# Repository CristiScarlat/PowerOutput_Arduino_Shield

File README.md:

# PowerOutput_Arduino_Shield
Arduino Mega Shield 16 x open collector(ULN2803) outputs I2C(MCP23017)

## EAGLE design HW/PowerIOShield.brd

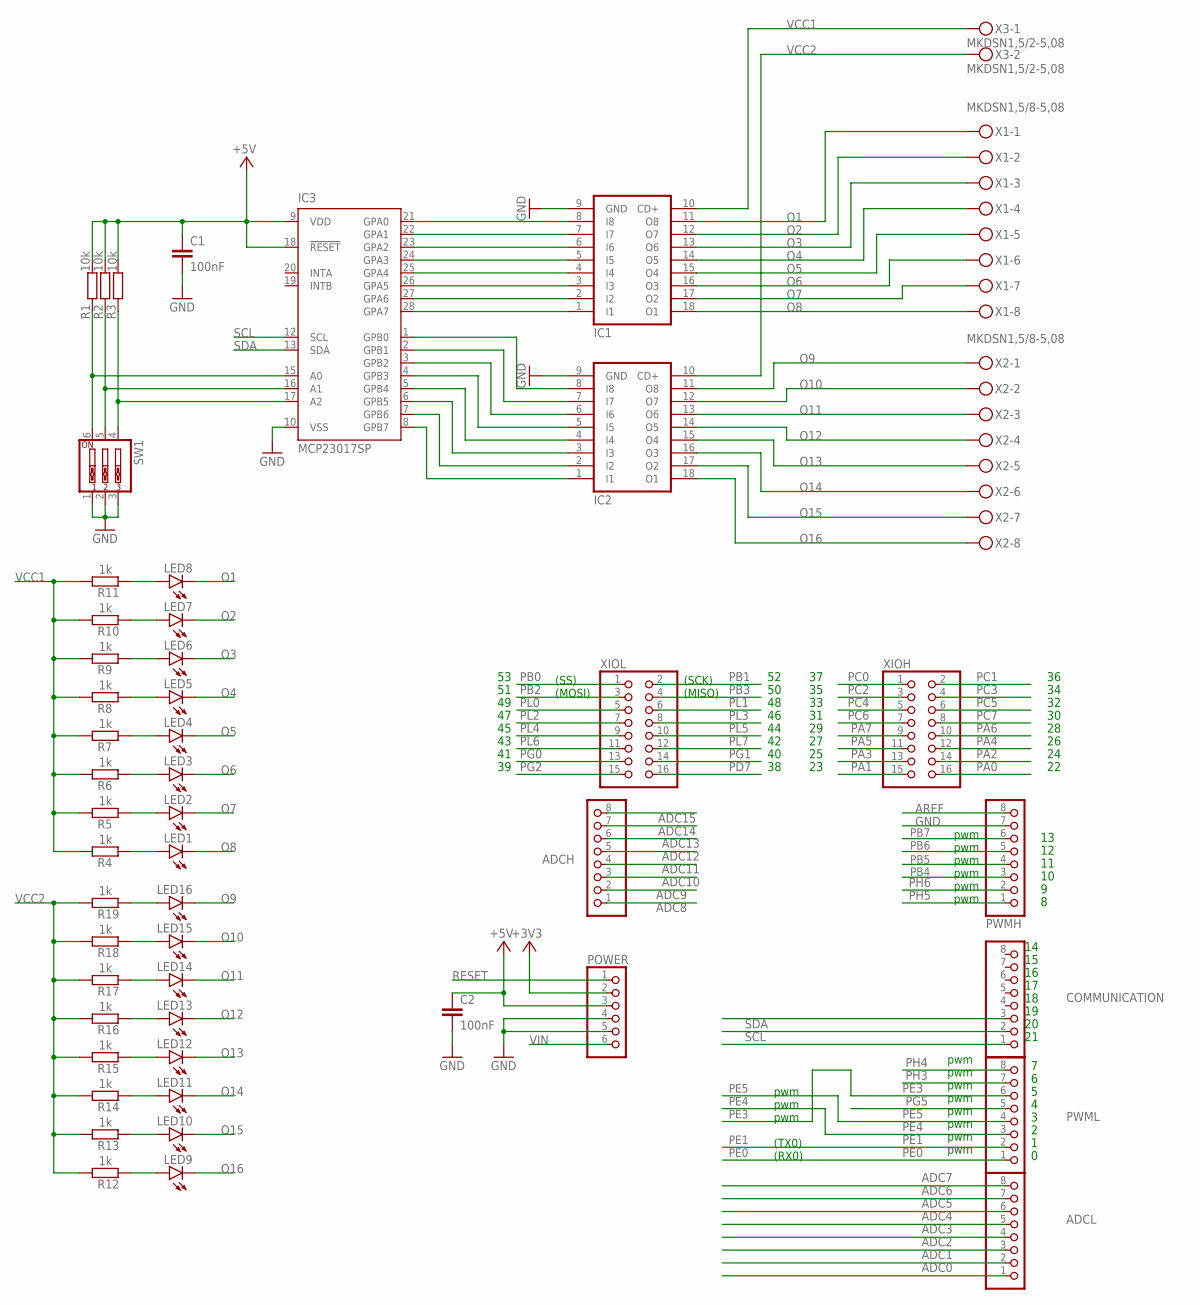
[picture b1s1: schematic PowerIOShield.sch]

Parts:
ADCH: PINHD-1X8; 1X08
ADCL: PINHD-1X8; 1X08
C1, C2: 100nF; C025-024X044
COMMUNICATION: PINHD-1X8; 1X08
IC1, IC2: ULN2803A; DIL18
IC3: MCP23017SP; DIL28-3
LED1, LED2, LED3, LED4, LED5, LED6, LED7, LED8, LED9, LED10, LED11, LED12, LED13, LED14, LED15, LED16: LED3MM
POWER: PINHD-1X6; 1X06
PWMH: PINHD-1X8; 1X08
PWML: PINHD-1X8; 1X08
R1, R2, R3: 10k; 0204/7
R4, R5, R6, R7, R8, R9, R10, R11, R12, R13, R14, R15, R16, R17, R18, R19: 1k; 0204/7
SW1: SW_DIP-3; EDG-03
X1, X2: MKDSN1,5/8-5,08
X3: MKDSN1,5/2-5,08
XIOH: PINHD-2X8; 2X08
XIOL: PINHD-2X8; 2X08

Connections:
+3V3: POWER.2
+5V: C1.1, C2.1, IC3.9 (VDD), IC3.18 (!RESET), POWER.3, R1.2, R2.2, R3.2
ADC0: ADCL.1
ADC1: ADCL.2
ADC2: ADCL.3
ADC3: ADCL.4
ADC4: ADCL.5
ADC5: ADCL.6
ADC6: ADCL.7
ADC7: ADCL.8
ADC8: ADCH.1
ADC9: ADCH.2
ADC10: ADCH.3
ADC11: ADCH.4
ADC12: ADCH.5
ADC13: ADCH.6
ADC14: ADCH.7
ADC15: ADCH.8
AREF: PWMH.8
GND: C1.2, C2.2, IC1.9 (GND), IC2.9 (GND), IC3.10 (VSS), POWER.4, POWER.5, PWMH.7, SW1.1, SW1.2, SW1.3
unnamed: IC3.15 (A0), R1.1, SW1.6
unnamed: IC2.8 (I8), IC3.1 (GPB0)
unnamed: IC1.1 (I1), IC3.28 (GPA7)
unnamed: IC1.2 (I2), IC3.27 (GPA6)
unnamed: IC1.3 (I3), IC3.26 (GPA5)
unnamed: IC1.4 (I4), IC3.25 (GPA4)
unnamed: IC1.5 (I5), IC3.24 (GPA3)
unnamed: IC1.6 (I6), IC3.23 (GPA2)
unnamed: IC1.7 (I7), IC3.22 (GPA1)
unnamed: IC1.8 (I8), IC3.21 (GPA0)
unnamed: IC2.7 (I7), IC3.2 (GPB1)
unnamed: IC2.6 (I6), IC3.3 (GPB2)
unnamed: IC2.5 (I5), IC3.4 (GPB3)
unnamed: IC2.4 (I4), IC3.5 (GPB4)
unnamed: IC2.3 (I3), IC3.6 (GPB5)
unnamed: IC2.2 (I2), IC3.7 (GPB6)
unnamed: IC2.1 (I1), IC3.8 (GPB7)
unnamed: IC3.16 (A1), R2.1, SW1.5
unnamed: IC3.17 (A2), R3.1, SW1.4
unnamed: LED1.A, R4.1
unnamed: LED2.A, R5.1
unnamed: LED3.A, R6.1
unnamed: LED4.A, R7.1
unnamed: LED5.A, R8.1
unnamed: LED6.A, R9.1
unnamed: LED7.A, R10.1
unnamed: LED8.A, R11.1
unnamed: LED9.A, R12.1
unnamed: LED10.A, R13.1
unnamed: LED11.A, R14.1
unnamed: LED12.A, R15.1
unnamed: LED13.A, R16.1
unnamed: LED14.A, R17.1
unnamed: LED15.A, R18.1
unnamed: LED16.A, R19.1
O1: IC1.11 (O8), LED8.K (C), X1.1
O2: IC1.12 (O7), LED7.K (C), X1.2
O3: IC1.13 (O6), LED6.K (C), X1.3
O4: IC1.14 (O5), LED5.K (C), X1.4
O5: IC1.15 (O4), LED4.K (C), X1.5
O6: IC1.16 (O3), LED3.K (C), X1.6
O7: IC1.17 (O2), LED2.K (C), X1.7
O8: IC1.18 (O1), LED1.K (C), X1.8
O9: IC2.11 (O8), LED16.K (C), X2.1
O10: IC2.12 (O7), LED15.K (C), X2.2
O11: IC2.13 (O6), LED14.K (C), X2.3
O12: IC2.14 (O5), LED13.K (C), X2.4
O13: IC2.15 (O4), LED12.K (C), X2.5
O14: IC2.16 (O3), LED11.K (C), X2.6
O15: IC2.17 (O2), LED10.K (C), X2.7
O16: IC2.18 (O1), LED9.K (C), X2.8
PA0: XIOH.16
PA1: XIOH.15
PA2: XIOH.14
PA3: XIOH.13
PA4: XIOH.12
PA5: XIOH.11
PA6: XIOH.10
PA7: XIOH.9
PB0: XIOL.1
PB1: XIOL.2
PB2: XIOL.3
PB3: XIOL.4
PB4: PWMH.3
PB5: PWMH.4
PB6: PWMH.5
PB7: PWMH.6
PC0: XIOH.1
PC1: XIOH.2
PC2: XIOH.3
PC3: XIOH.4
PC4: XIOH.5
PC5: XIOH.6
PC6: XIOH.7
PC7: XIOH.8
PD7: XIOL.16
PE0: PWML.1
PE1: PWML.2
PE3: PWML.6
PE4: PWML.3
PE5: PWML.4
PG0: XIOL.13
PG1: XIOL.14
PG2: XIOL.15
PG5: PWML.5
PH3: PWML.7
PH4: PWML.8
PH5: PWMH.1
PH6: PWMH.2
PL0: XIOL.5
PL1: XIOL.6
PL2: XIOL.7
PL3: XIOL.8
PL4: XIOL.9
PL5: XIOL.10
PL6: XIOL.11
PL7: XIOL.12
RESET: POWER.1
RXD1: COMMUNICATION.3
SCL: COMMUNICATION.1, IC3.12 (SCL)
SDA: COMMUNICATION.2, IC3.13 (SDA)
VCC1: IC1.10 (CD+), R4.2, R5.2, R6.2, R7.2, R8.2, R9.2, R10.2, R11.2, X3.1
VCC2: IC2.10 (CD+), R12.2, R13.2, R14.2, R15.2, R16.2, R17.2, R18.2, R19.2, X3.2
VIN: POWER.6

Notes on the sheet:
pwm
(TX0)
(RX0)
(SS)
(MOSI)
(SCK)
(MISO)

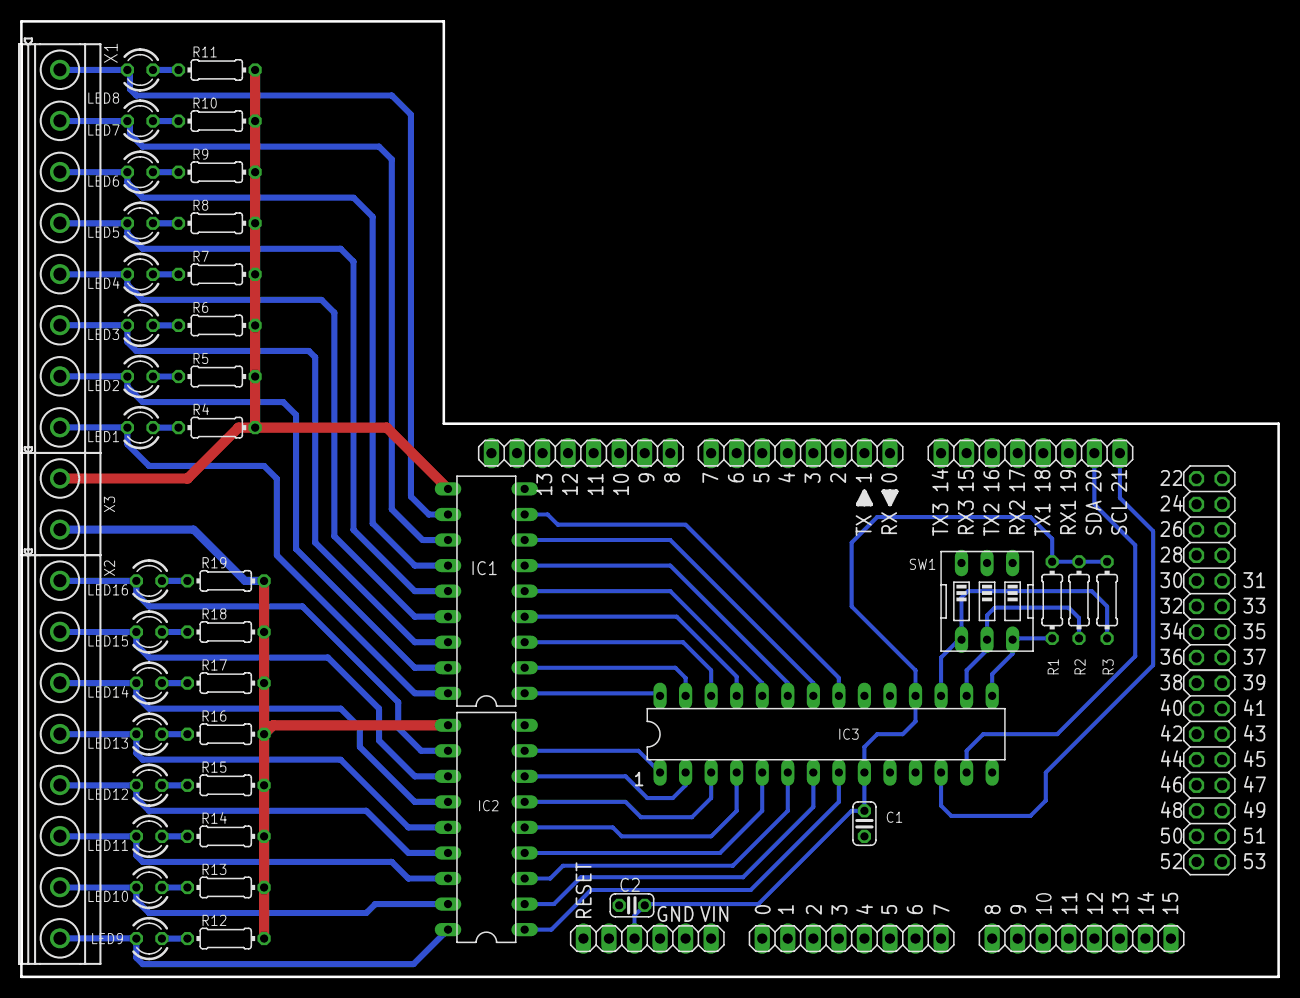
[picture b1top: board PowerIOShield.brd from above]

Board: 2 copper layers, 125.0 x 95.0 mm, 52 parts (0 on the bottom side), 57 nets.

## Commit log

2019-04-11 top silk added, regenerate gerber files
